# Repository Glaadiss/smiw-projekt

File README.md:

### Alarm wilgotności i temperatury

## Bartłomiej Gładys INF sem 5

Urządzenie sprawdza wilgotność i temperaturę w pomieszczeniu. Informuje użytkownika gdy jest sucho poprzez wysłanie powiadomienia na aplikacje mobilną. Użytkownik sam wcześniej deklaruje zakresy temperatur i wilgotności, w których zostanie powiadomiony. Dodatkowo urządzenie odczytuje poprzez zewnętrzny serwis informację pogodowe na zewnątrz pomieszczenia.

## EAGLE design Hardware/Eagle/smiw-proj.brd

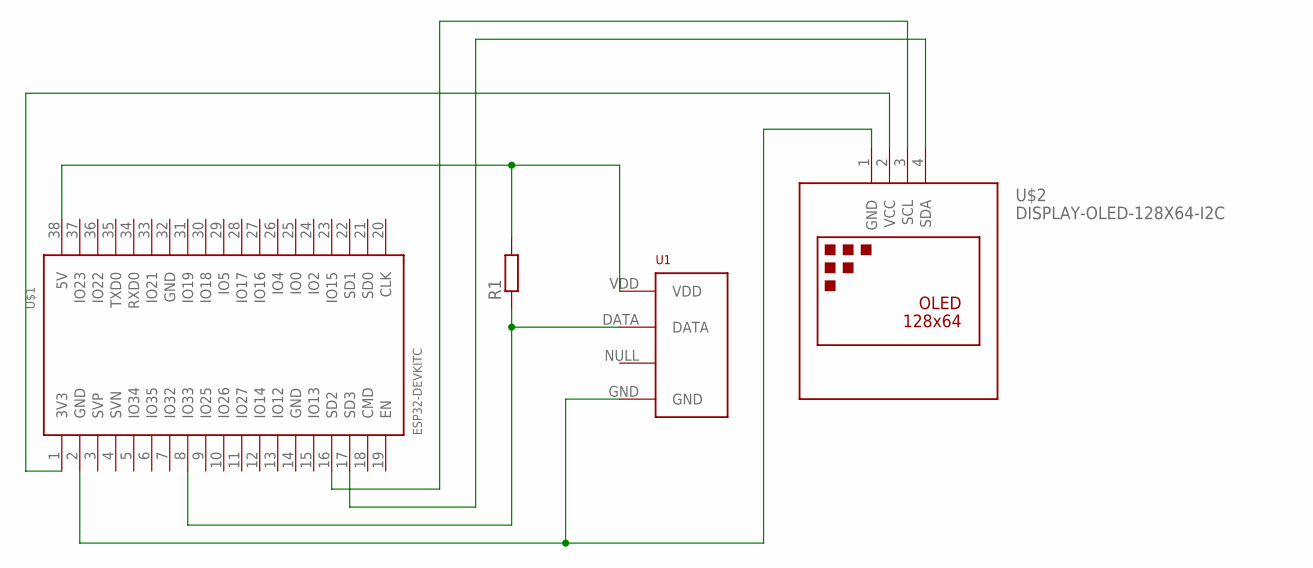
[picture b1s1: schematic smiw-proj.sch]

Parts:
R1: R0204/7; 0204/7
U1: RHT03_DHT-22_AM2302RA; RHT03_DHT-22/RA
U$1: ESP32DEVKITC; ESP32-DEVKITC
U$2: DISPLAY-OLED-128X64-I2C

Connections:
unnamed: R1.1, U1.DATA, U$1.8 (IO33)
unnamed: R1.2, U1.VDD, U$1.38 (5V)
unnamed: U$1.1 (3V3), U$2.2 (VCC)
unnamed: U1.GND, U$1.2 (GND), U$2.1 (GND)
unnamed: U$1.17 (SD3), U$2.4 (SDA)
unnamed: U$1.16 (SD2), U$2.3 (SCL)

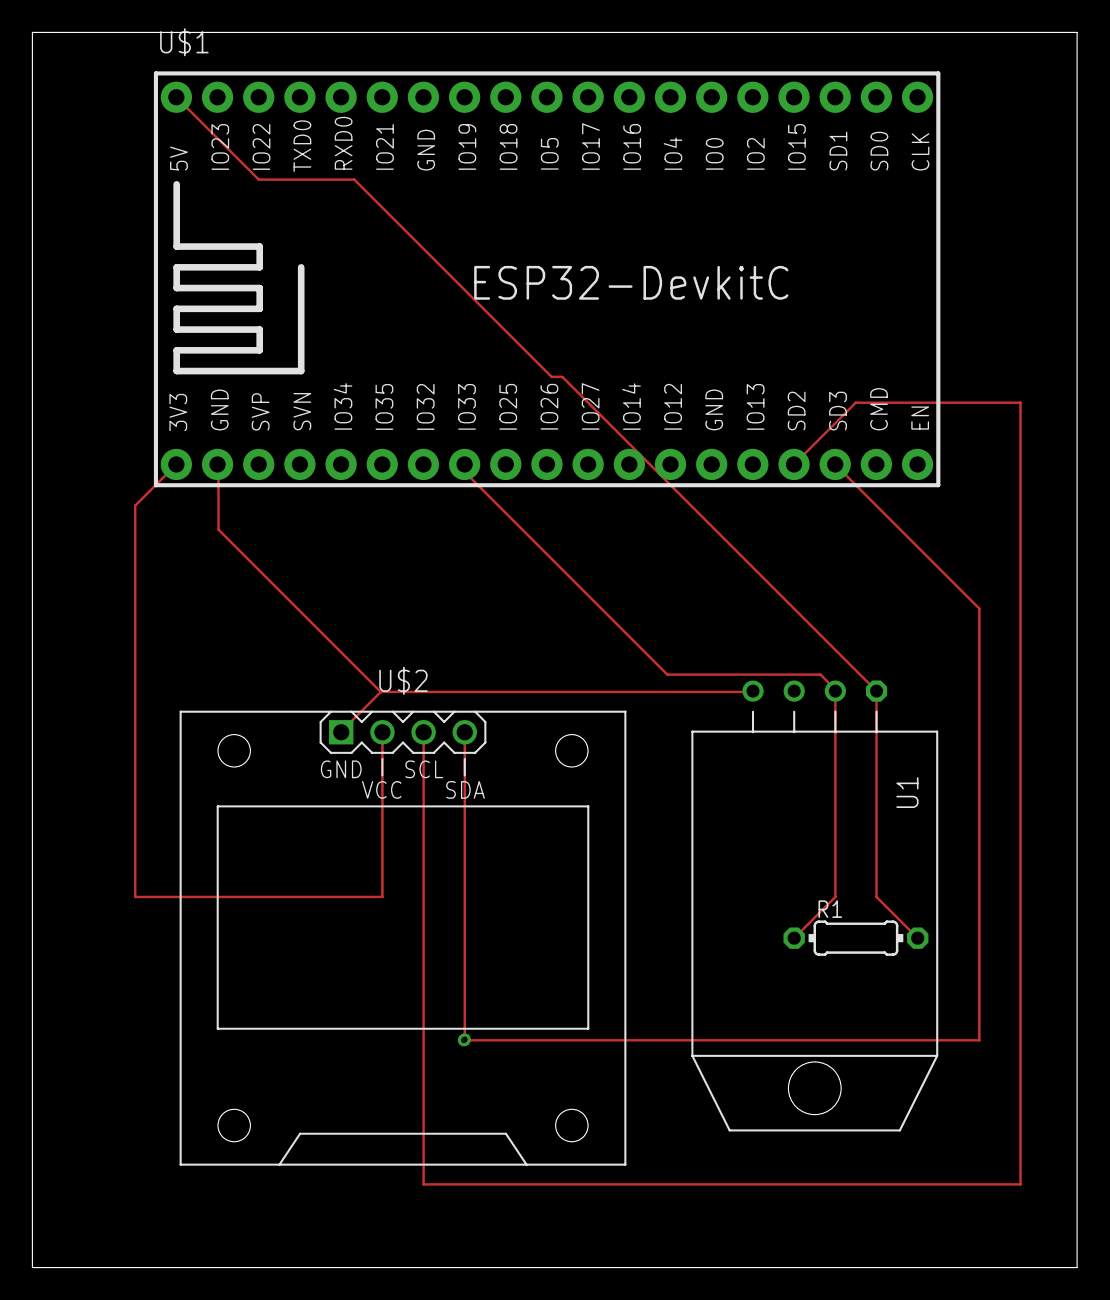
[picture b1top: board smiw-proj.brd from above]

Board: 2 copper layers, 64.4 x 76.2 mm, 4 parts (0 on the bottom side), 6 nets.

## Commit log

2019-01-13 Add report

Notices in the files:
parts and their libraries:
oled09: Released under the Creative Commons Attribution 4.0 International License: http://creativecommons.org/licenses/by/4.0
